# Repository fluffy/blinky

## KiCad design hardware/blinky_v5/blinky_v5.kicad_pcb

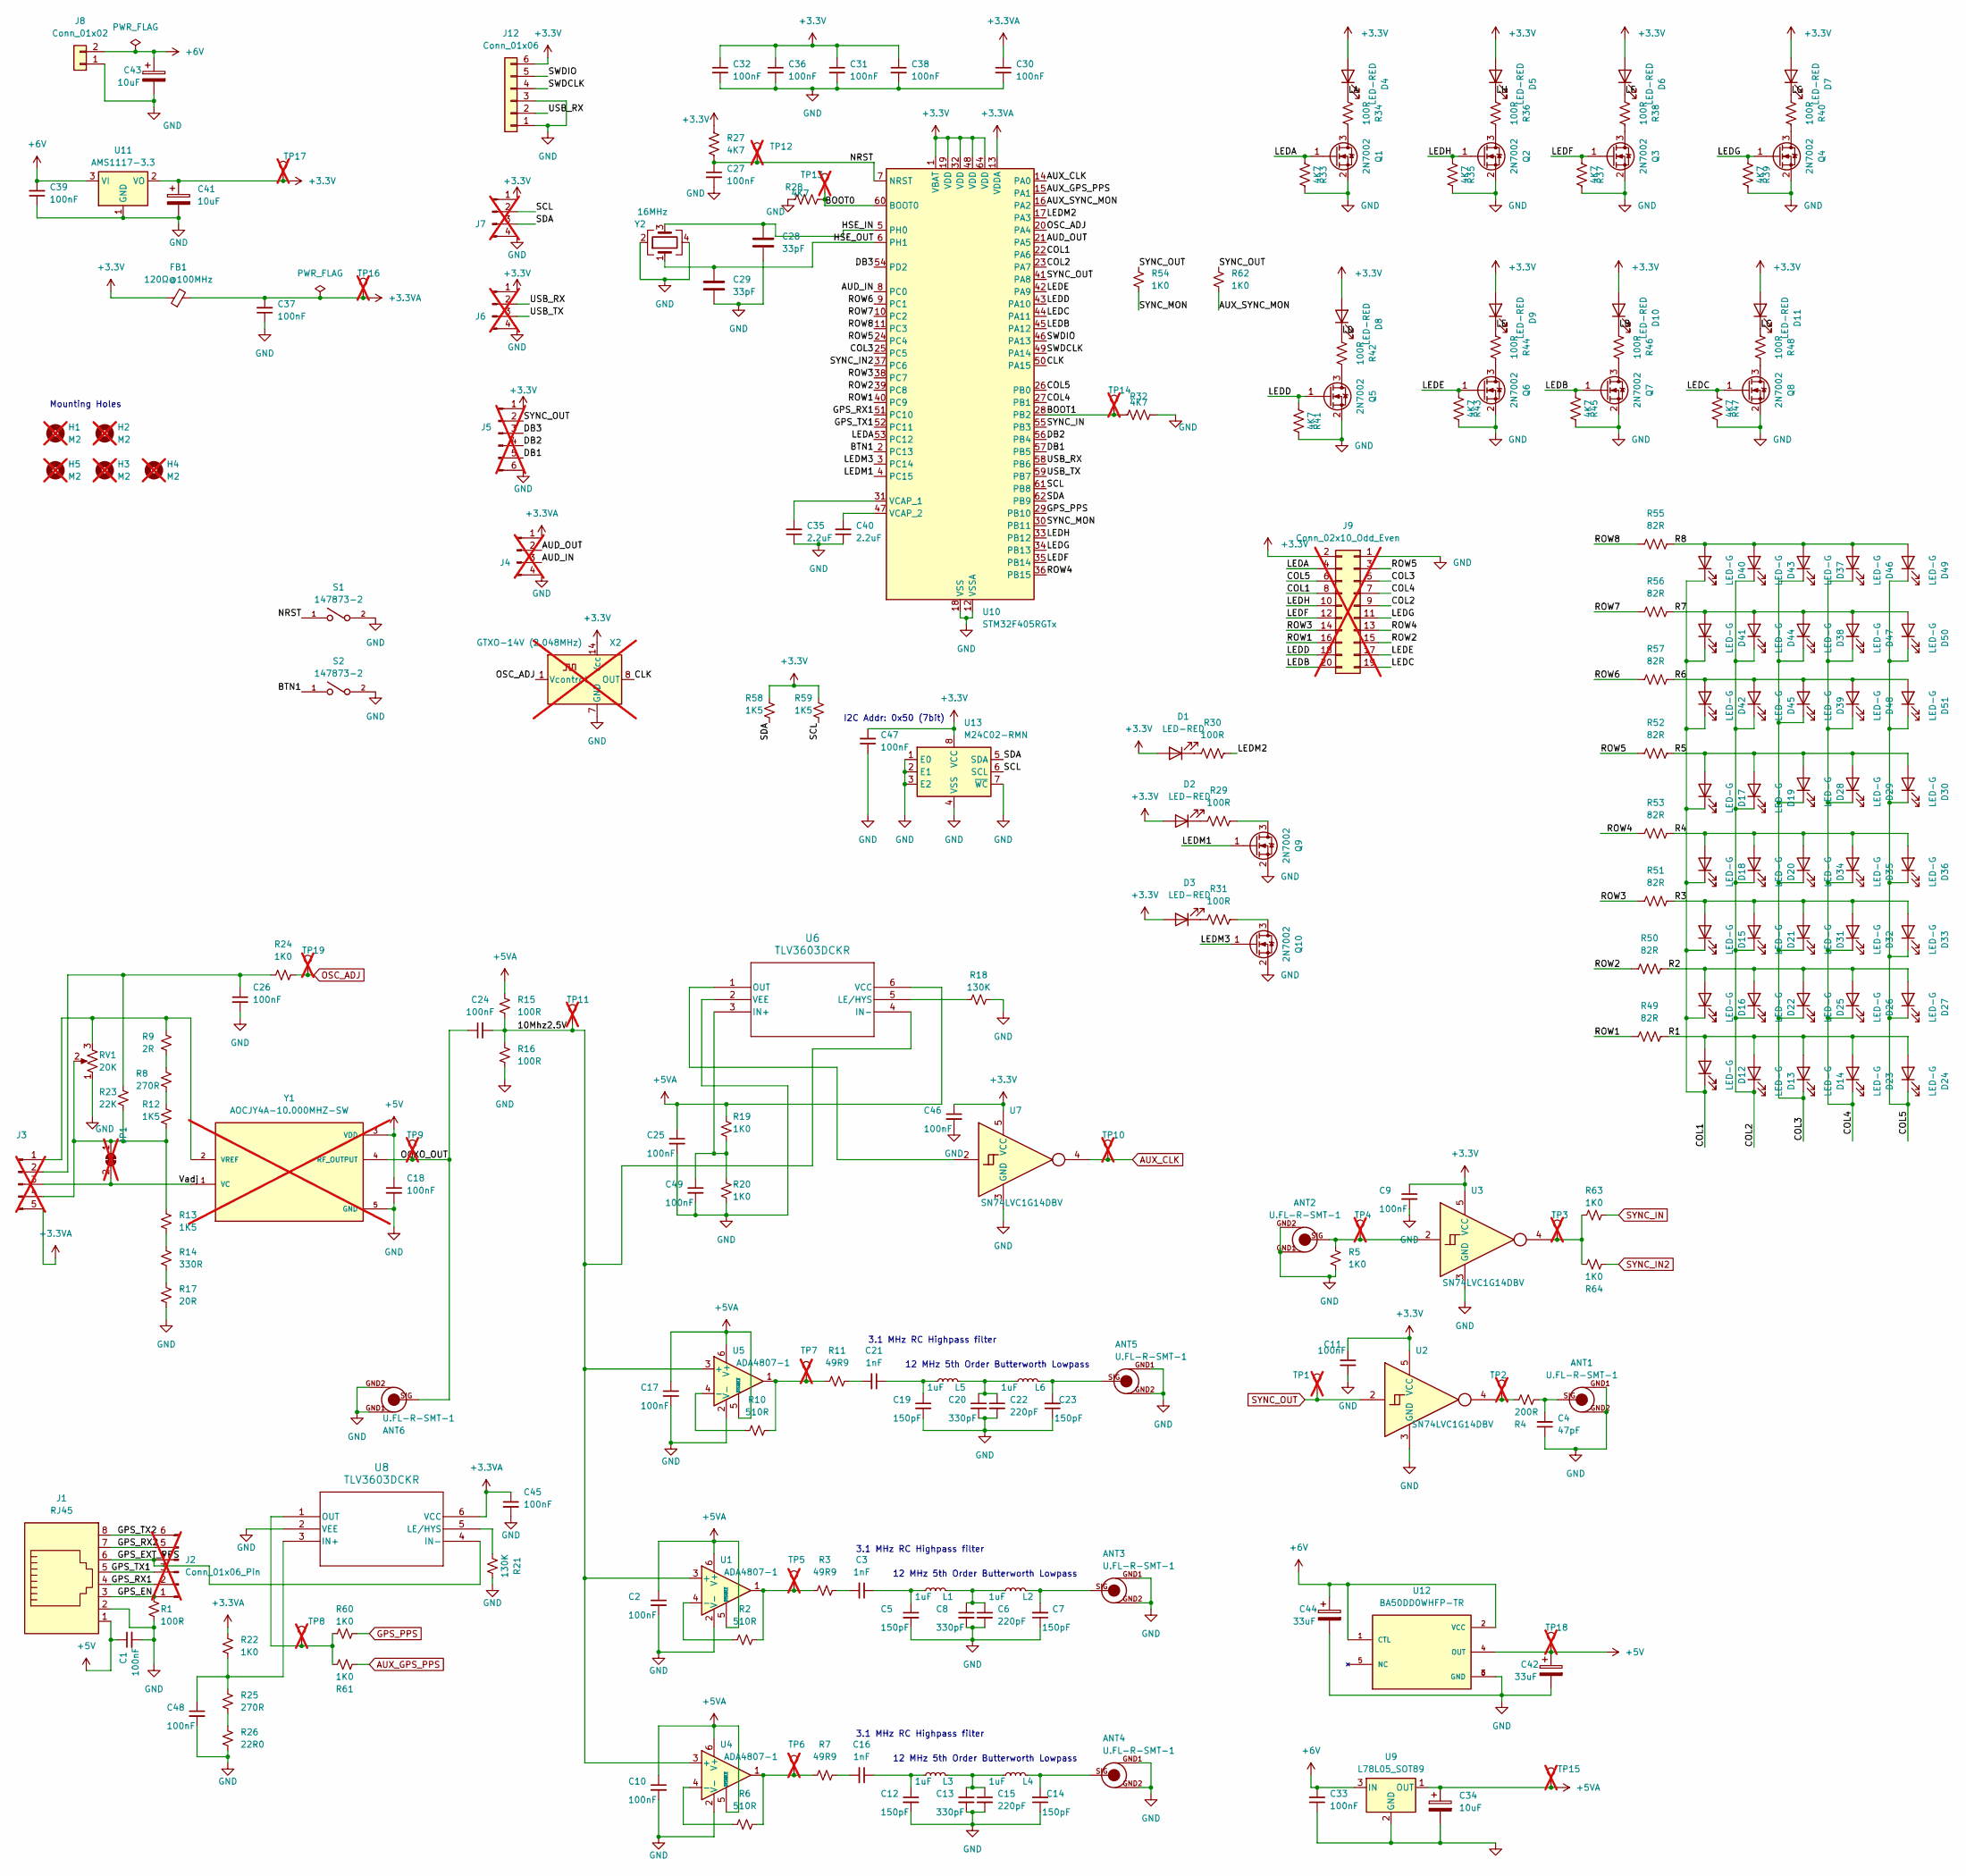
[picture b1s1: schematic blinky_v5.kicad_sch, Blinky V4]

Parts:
ANT1, ANT2, ANT3, ANT4, ANT5, ANT6: U.FL-R-SMT-1; LCSC C88374
C1, C2, C9, C10, C11, C17, C18, C25, C26, C30, C31, C32, C33, C36, C38, C39, C45, C46, C47, C48, C49: 100nF; C_0402_1005Metric; LCSC C307331
C3, C16, C21: 1nF; C_0603_1608Metric; LCSC C1588
C4: 47pF; C_0805_2012Metric; LCSC C14857
C5, C7, C12, C14, C19, C23: 150pF; C_0603_1608Metric; LCSC C1594
C6, C15, C22: 220pF; C_0603_1608Metric; LCSC C1603
C8, C13, C20: 330pF; C_0603_1608Metric; LCSC C1664
C24, C27, C37: 100nF; C_0603_1608Metric; LCSC C14663
C28, C29: 33pF; C_0603_1608Metric; LCSC C1663
C34, C41, C43: 10uF; CP_EIA-3216-18_Kemet-A; LCSC C7171
C35, C40: 2.2uF; C_0603_1608Metric; LCSC C23630
C42, C44: 33uF; CP_EIA-3528-21_Kemet-B; LCSC C128342
D1, D2, D3, D4, D5, D6, D7, D8, D9, D10, D11: LED-RED; LED_0603_1608Metric; LCSC C94869
D12, D13, D14, D15, D16, D17, D18, D19, D20, D21, D22, D23, D24, D25, D26, D27, D28, D29, D30, D31, D32, D33, D34, D35, D36, D37, D38, D39, D40, D41, D42, D43, D44, D45, D46, D47, D48, D49, D50, D51: LED-G; LED_0603_1608Metric; LCSC C125093
FB1: 120Ω@100MHz; R_0603_1608Metric; LCSC C127301
H1, H2, H3, H4, H5: M2; MountingHole_2.2mm_M2; not fitted
J1: RJ45; RJ45_Amphenol_RJHSE5380; LCSC C464586
J2, J5: Conn_01x06_Pin; PinHeader_1x06_P2.54mm_Vertical; not fitted
J3: Conn_01x05_Pin; PinHeader_1x05_P2.54mm_Vertical; not fitted
J4, J6, J7: Conn_01x04_Pin; PinHeader_1x04_P2.54mm_Vertical; not fitted
J8: Conn_01x02; JST_PH_S2B-PH-SM4-TB_1x02-1MP_P2.00mm_Horizontal; LCSC C295747
J9: Conn_02x10_Odd_Even; PinHeader_2x10_P2.54mm_Vertical; not fitted
J12: Conn_01x06; JST_PH_S6B-PH-SM4-TB_1x06-1MP_P2.00mm_Horizontal; LCSC C265405
JP1: SolderJumper_2_Bridged; SolderJumper-2_P1.3mm_Bridged_RoundedPad1.0x1.5mm; not fitted
L1, L2, L3, L4, L5, L6: 1uF; L_0805_2012Metric; LCSC C1042
Q1, Q2, Q3, Q4, Q5, Q6, Q7, Q8, Q9, Q10: 2N7002; SOT-23; LCSC C8545
R1, R15, R16, R29, R30, R31, R34, R36, R38, R40, R42, R44, R46, R48: 100R; R_0603_1608Metric; LCSC C22775
R2, R6, R10: 510R; R_0603_1608Metric; LCSC C23193
R3, R7, R11: 49R9; R_0603_1608Metric; LCSC C23185
R4: 200R; R_0805_2012Metric; LCSC C17540
R5, R19, R20, R22, R24, R54, R60, R61, R62, R63, R64: 1K0; R_0603_1608Metric; LCSC C21190
R8: 270R; R_0805_2012Metric; LCSC C17590
R9: 2R; R_0805_2012Metric; LCSC C17606
R12, R13: 1K5; R_0805_2012Metric; LCSC C4310
R14: 330R; R_0805_2012Metric; LCSC C17630
R17: 20R; R_0805_2012Metric; LCSC C17544
R18, R21: 130K; R_0603_1608Metric; LCSC C22795
R23: 22K; R_0805_2012Metric; LCSC C17560
R25: 270R; R_0603_1608Metric; LCSC C22966
R26: 22R0; R_0603_1608Metric; LCSC C23345
R27, R28, R32, R33, R35, R37, R39, R41, R43, R45, R47: 4K7; R_0603_1608Metric; LCSC C23162
R49, R50, R51, R52, R53, R55, R56, R57: 82R; R_0603_1608Metric; LCSC C23255
R58, R59: 1K5; R_0603_1608Metric; LCSC C22843
RV1: 20K; Potentiometer_Bourns_3314G_Vertical; LCSC C780217
S1, S2: 147873-2; SW_147873-2
TP1, TP2, TP3, TP4, TP5, TP6, TP7, TP8, TP9, TP10, TP11, TP12, TP13, TP14, TP15, TP16, TP17, TP18, TP19: TestPoint_THTPad_D1.5mm_Drill0.7mm; not fitted
U1, U4, U5: ADA4807-1; SOT-23-6; LCSC C2058411
U2, U3, U7: SN74LVC1G14DBV; SOT-23-5; LCSC C133145
U6, U8: TLV3603DCKR; SC70_DCK_TEX; LCSC C5213955
U9: L78L05_SOT89; SOT-89-3; LCSC C71136
U10: STM32F405RGTx; LQFP-64_10x10mm_P0.5mm; LCSC C15742
U11: AMS1117-3.3; SOT-223-3_TabPin2; LCSC C6186
U12: BA50DD0WHFP-TR; DPAK172P1054X200-6N; PARTREV 003; LCSC C509718
U13: M24C02-RMN; SOIC-8_3.9x4.9mm_P1.27mm; LCSC C83836
X2: GTXO-14V (2.048MHz); Oscillator_DIP-14; not fitted
Y1: AOCJY4A-10.000MHZ-SW; XTAL_AOCJY4A-10.000MHZ-SW; PARTREV 07.24.11; LCSC C1670487; not fitted
Y2: 16MHz; Crystal_SMD_3225-4Pin_3.2x2.5mm; LCSC C13738

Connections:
+3.3V: C9.1, C11.1, C31.1, C32.1, C36.1, C38.1, C41.1, C46.1, C47.2, D1.2 (A), D2.2 (A), D3.2 (A), D4.2 (A), D5.2 (A), D6.2 (A), D7.2 (A), D8.2 (A), D9.2 (A), D10.2 (A), D11.2 (A), FB1.1, J5.1, J6.1, J7.1, J9.2, J12.6, R27.1, R58.1, R59.1, TP17.1, U2.5 (VCC), U3.5 (VCC), U7.5 (VCC), U10.1 (VBAT), U10.19 (VDD), U10.32 (VDD), U10.48 (VDD), U10.64 (VDD), U11.2 (VO), U13.8 (VCC), X2.14 (Vcc)
+3.3VA: C30.1, C37.2, C45.1, FB1.2, J3.5, J4.1, R22.1, TP16.1, U8.6 (VCC), U10.13 (VDDA)
+5V: C1.1, C18.1, C42.1, J1.1, TP18.1, U12.4 (OUT), Y1.3 (VDD)
+5VA: C2.1, C10.1, C17.1, C25.1, C34.1, R15.1, R19.1, TP15.1, U1.5 (~DISABLE), U1.6 (V+), U4.5 (~DISABLE), U4.6 (V+), U5.5 (~DISABLE), U5.6 (V+), U6.6 (VCC), U9.1 (OUT)
+6V: C33.2, C39.2, C43.1, C44.1, J8.2, U9.3 (IN), U11.3 (VI), U12.1 (CTL), U12.2 (VCC)
/10Mhz2.5V: C24.2, R15.2, R16.1, TP11.1, U1.3 (+), U4.3 (+), U5.3 (+), U6.4 (IN-)
/AUD_IN: J4.3, U10.8 (PC0)
/AUD_OUT: J4.2, U10.21 (PA5)
/AUX_SYNC_MON: R62.2, U10.16 (PA2)
/BOOT0: R28.1, TP13.1, U10.60 (BOOT0)
/BOOT1: R32.2, TP14.1, U10.28 (PB2)
/BTN1: S2.1, U10.2 (PC13)
/CLK: U10.50 (PA15), X2.8 (OUT)
/COL1: D12.1 (K), D15.1 (K), D16.1 (K), D17.1 (K), D18.1 (K), D40.1 (K), D41.1 (K), D42.1 (K), J9.8, U10.22 (PA6)
/COL2: D13.1 (K), D19.1 (K), D20.1 (K), D21.1 (K), D22.1 (K), D43.1 (K), D44.1 (K), D45.1 (K), J9.9, U10.23 (PA7)
/COL3: D14.1 (K), D25.1 (K), D28.1 (K), D31.1 (K), D34.1 (K), D37.1 (K), D38.1 (K), D39.1 (K), J9.5, U10.25 (PC5)
/COL4: D23.1 (K), D26.1 (K), D29.1 (K), D32.1 (K), D35.1 (K), D46.1 (K), D47.1 (K), D48.1 (K), J9.7, U10.27 (PB1)
/COL5: D24.1 (K), D27.1 (K), D30.1 (K), D33.1 (K), D36.1 (K), D49.1 (K), D50.1 (K), D51.1 (K), J9.6, U10.26 (PB0)
/DB1: J5.5, U10.57 (PB5)
/DB2: J5.4, U10.56 (PB4)
/DB3: J5.3, U10.54 (PD2)
/GPS_EN: J1.3, J2.1, R1.1
/GPS_EXT_PPS: J1.6, J2.4, U8.4 (IN-)
/GPS_RX1: J1.4, J2.2, U10.51 (PC10)
/GPS_RX2: J1.7, J2.5
/GPS_TX1: J1.5, J2.3, U10.52 (PC11)
/GPS_TX2: J1.8, J2.6
/HSE_IN: C28.1, U10.5 (PH0), Y2.3
/HSE_OUT: C29.1, U10.6 (PH1), Y2.1
/LA: D4.1 (K), R34.1
/LB: D10.1 (K), R46.1
/LC: D11.1 (K), R48.1
/LD: D8.1 (K), R42.1
/LE: D9.1 (K), R44.1
/LEDA: J9.4, Q1.1 (G), R33.2, U10.53 (PC12)
/LEDB: J9.20, Q7.1 (G), R45.2, U10.45 (PA12)
/LEDC: J9.19, Q8.1 (G), R47.2, U10.44 (PA11)
/LEDD: J9.18, Q5.1 (G), R41.2, U10.43 (PA10)
/LEDE: J9.17, Q6.1 (G), R43.2, U10.42 (PA9)
/LEDF: J9.12, Q3.1 (G), R37.2, U10.35 (PB14)
/LEDG: J9.11, Q4.1 (G), R39.2, U10.34 (PB13)
/LEDH: J9.10, Q2.1 (G), R35.2, U10.33 (PB12)
/LEDM1: Q9.1 (G), U10.4 (PC15)
/LEDM2: R30.2, U10.17 (PA3)
/LEDM3: Q10.1 (G), U10.3 (PC14)
/LF: D6.1 (K), R38.1
/LG: D7.1 (K), R40.1
/LH: D5.1 (K), R36.1
/NRST: C27.1, R27.2, S1.1, TP12.1, U10.7 (NRST)
/OCXO_OUT: ANT6.SIG, C24.1, TP9.1, Y1.4 (RF_OUTPUT)
/R1: D12.2 (A), D13.2 (A), D14.2 (A), D23.2 (A), D24.2 (A), R49.1
/R2: D16.2 (A), D22.2 (A), D25.2 (A), D26.2 (A), D27.2 (A), R50.1
/R3: D15.2 (A), D21.2 (A), D31.2 (A), D32.2 (A), D33.2 (A), R51.1
/R4: D18.2 (A), D20.2 (A), D34.2 (A), D35.2 (A), D36.2 (A), R53.1
/R5: D17.2 (A), D19.2 (A), D28.2 (A), D29.2 (A), D30.2 (A), R52.1
/R6: D39.2 (A), D42.2 (A), D45.2 (A), D48.2 (A), D51.2 (A), R57.1
/R7: D38.2 (A), D41.2 (A), D44.2 (A), D47.2 (A), D50.2 (A), R56.1
/R8: D37.2 (A), D40.2 (A), D43.2 (A), D46.2 (A), D49.2 (A), R55.1
/ROW1: J9.16, R49.2, U10.40 (PC9)
/ROW2: J9.15, R50.2, U10.39 (PC8)
/ROW3: J9.14, R51.2, U10.38 (PC7)
/ROW4: J9.13, R53.2, U10.36 (PB15)
/ROW5: J9.3, R52.2, U10.24 (PC4)
/ROW6: R57.2, U10.9 (PC1)
/ROW7: R56.2, U10.10 (PC2)
/ROW8: R55.2, U10.11 (PC3)
/SCL: J7.2, R59.2, U10.61 (PB8), U13.6 (SCL)
/SDA: J7.3, R58.2, U10.62 (PB9), U13.5 (SDA)
/SWDCLK: J12.4, U10.49 (PA14)
/SWDIO: J12.5, U10.46 (PA13)
/SYNC_MON: R54.2, U10.30 (PB11)
/USB_RX: J6.2, J12.2, U10.58 (PB6)
/USB_TX: J6.3, U10.59 (PB7)
/Vadj: J3.3, JP1.2 (B), Y1.1 (VC)
AUX_CLK: TP10.1, U7.4, U10.14 (PA0)
AUX_GPS_PPS: R61.2, U10.15 (PA1)
GND: ANT1.GND1, ANT1.GND2, ANT2.GND1, ANT2.GND2, ANT3.GND1, ANT3.GND2, ANT4.GND1, ANT4.GND2, ANT5.GND1, ANT5.GND2, ANT6.GND1, ANT6.GND2, C1.2, C2.2, C4.1, C5.2, C6.2, C7.1, C8.2, C9.2, C10.2, C11.2, C12.2, C13.2, C14.1, C15.2, C17.2, C18.2, C19.2, C20.2, C22.2, C23.1, C25.2, C26.2, C27.2, C28.2, C29.2, C30.2, C31.2, C32.2, C33.1, C34.2, C35.1, C36.2, C37.1, C38.2, C39.1, C40.1, C41.2, C42.2, C43.2, C44.2, C45.2, C46.2, C47.1, C48.2, C49.2, J1.2, J4.4, J5.6, J6.4, J7.4, J8.1, J9.1, J12.1, J12.3, Q1.2 (S), Q2.2 (S), Q3.2 (S), Q4.2 (S), Q5.2 (S), Q6.2 (S), Q7.2 (S), Q8.2 (S), Q9.2 (S), Q10.2 (S), R1.2, R5.2, R16.2, R17.2, R18.2, R20.2, R21.2, R26.2, R28.2, R32.1, R33.1, R35.1, R37.1, R39.1, R41.1, R43.1, R45.1, R47.1, RV1.1, S1.2, S2.2, U1.2 (V-), U2.3 (GND), U3.3 (GND), U4.2 (V-), U5.2 (V-), U6.2 (VEE), U7.3 (GND), U8.2 (VEE), U9.2 (GND), U10.12 (VSSA), U10.18 (VSS), U10.63 (VSS), U11.1 (GND), U12.3 (GND), U12.6 (GND), U13.1 (E0), U13.2 (E1), U13.3 (E2), U13.4 (VSS), U13.7 (~WC), X2.7 (GND), Y1.5 (GND), Y2.2, Y2.4
GPS_PPS: R60.1, U10.29 (PB10)
unnamed: ANT1.SIG, C4.2, R4.2
unnamed: ANT2.SIG, R5.1, TP4.1, U3.2
unnamed: ANT3.SIG, C7.2, L2.1
unnamed: ANT4.SIG, C14.2, L4.1
unnamed: ANT5.SIG, C23.2, L6.1
unnamed: C3.1, C5.1, L1.1
unnamed: C3.2, R3.2
unnamed: C6.1, C8.1, L1.2, L2.2
unnamed: C12.1, C16.1, L3.1
unnamed: C13.1, C15.1, L3.2, L4.2
unnamed: C16.2, R7.2
unnamed: C19.1, C21.1, L5.1
unnamed: C20.1, C22.1, L5.2, L6.2
unnamed: C21.2, R11.2
unnamed: D1.1 (K), R30.1
unnamed: D2.1 (K), R29.1
unnamed: D3.1 (K), R31.1
unnamed: J3.1, R9.1, RV1.3, Y1.2 (VREF)
unnamed: C26.1, J3.2, R23.1, R24.1
unnamed: J3.4, JP1.1 (A), R12.2, R13.1, R23.2, RV1.2
unnamed: Q1.3 (D), R34.2
unnamed: Q2.3 (D), R36.2
unnamed: Q3.3 (D), R38.2
unnamed: Q4.3 (D), R40.2
unnamed: Q5.3 (D), R42.2
unnamed: Q6.3 (D), R44.2
unnamed: Q7.3 (D), R46.2
unnamed: Q8.3 (D), R48.2
unnamed: Q9.3 (D), R29.2
unnamed: Q10.3 (D), R31.2
unnamed: R2.2, R3.1, TP5.1, U1.1
unnamed: R4.1, TP2.1, U2.4
unnamed: R6.2, R7.1, TP6.1, U4.1
unnamed: R8.1, R9.2
unnamed: R10.2, R11.1, TP7.1, U5.1
unnamed: R8.2, R12.1
unnamed: R13.2, R14.1
unnamed: R14.2, R17.1
unnamed: R25.2, R26.1
unnamed: R63.2, R64.2, TP3.1, U3.4
unnamed: R2.1, U1.4 (-)
unnamed: R6.1, U4.4 (-)
unnamed: R10.1, U5.4 (-)
unnamed: C49.1, R19.2, R20.1, U6.3 (IN+)
unnamed: R18.1, U6.5 (LE/HYS)
unnamed: U6.1 (OUT), U7.2
unnamed: C48.1, R22.2, R25.1, U8.3 (IN+)
unnamed: R21.1, U8.5 (LE/HYS)
unnamed: R60.2, R61.1, TP8.1, U8.1 (OUT)
unnamed: C35.2, U10.31 (VCAP_1)
unnamed: C40.2, U10.47 (VCAP_2)
OSC_ADJ: R24.2, TP19.1, U10.20 (PA4), X2.1 (Vcontrol)
SYNC_IN: R63.1, U10.55 (PB3)
SYNC_IN2: R64.1, U10.37 (PC6)
SYNC_OUT: J5.2, R54.1, R62.1, TP1.1, U2.2, U10.41 (PA8)

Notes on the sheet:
3.1 MHz RC Highpass filter
12 MHz 5th Order Butterworth Lowpass
I2C Addr: 0x50 (7bit)
Mounting Holes

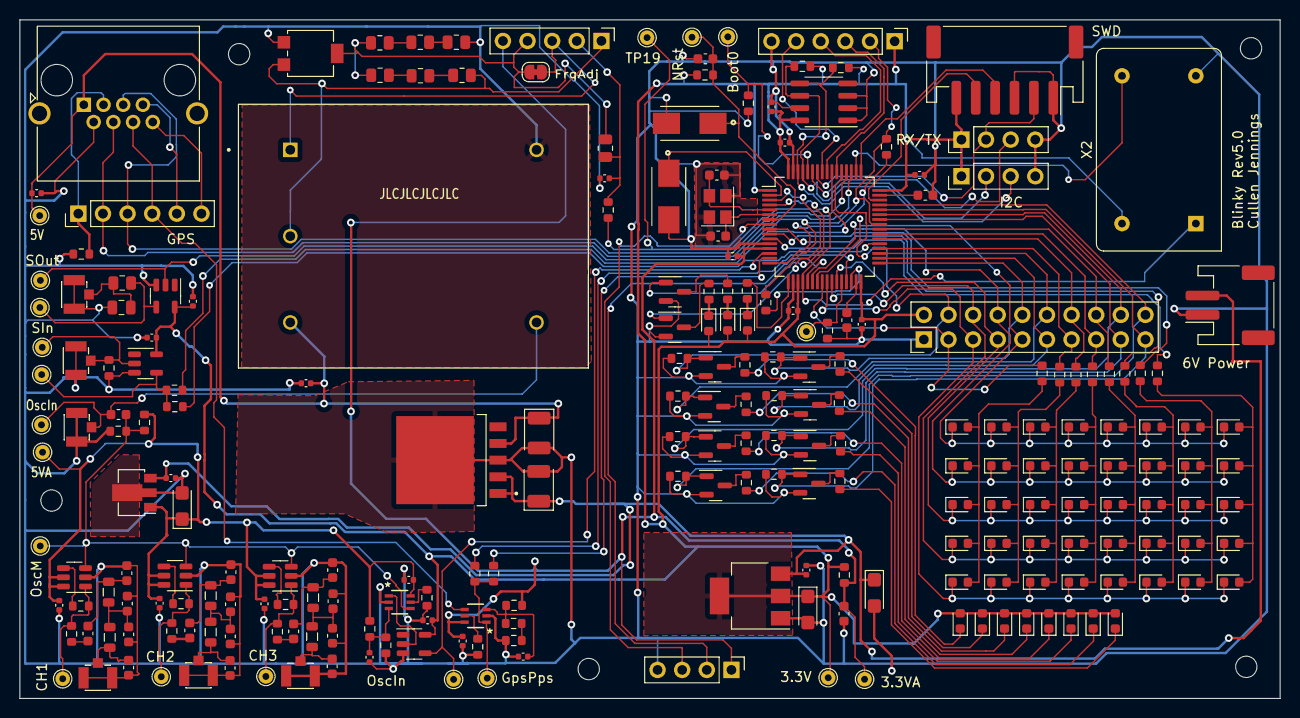
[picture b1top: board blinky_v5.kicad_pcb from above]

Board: 2 copper layers, 130.0 x 70.0 mm, 241 parts (0 on the bottom side), 133 nets.

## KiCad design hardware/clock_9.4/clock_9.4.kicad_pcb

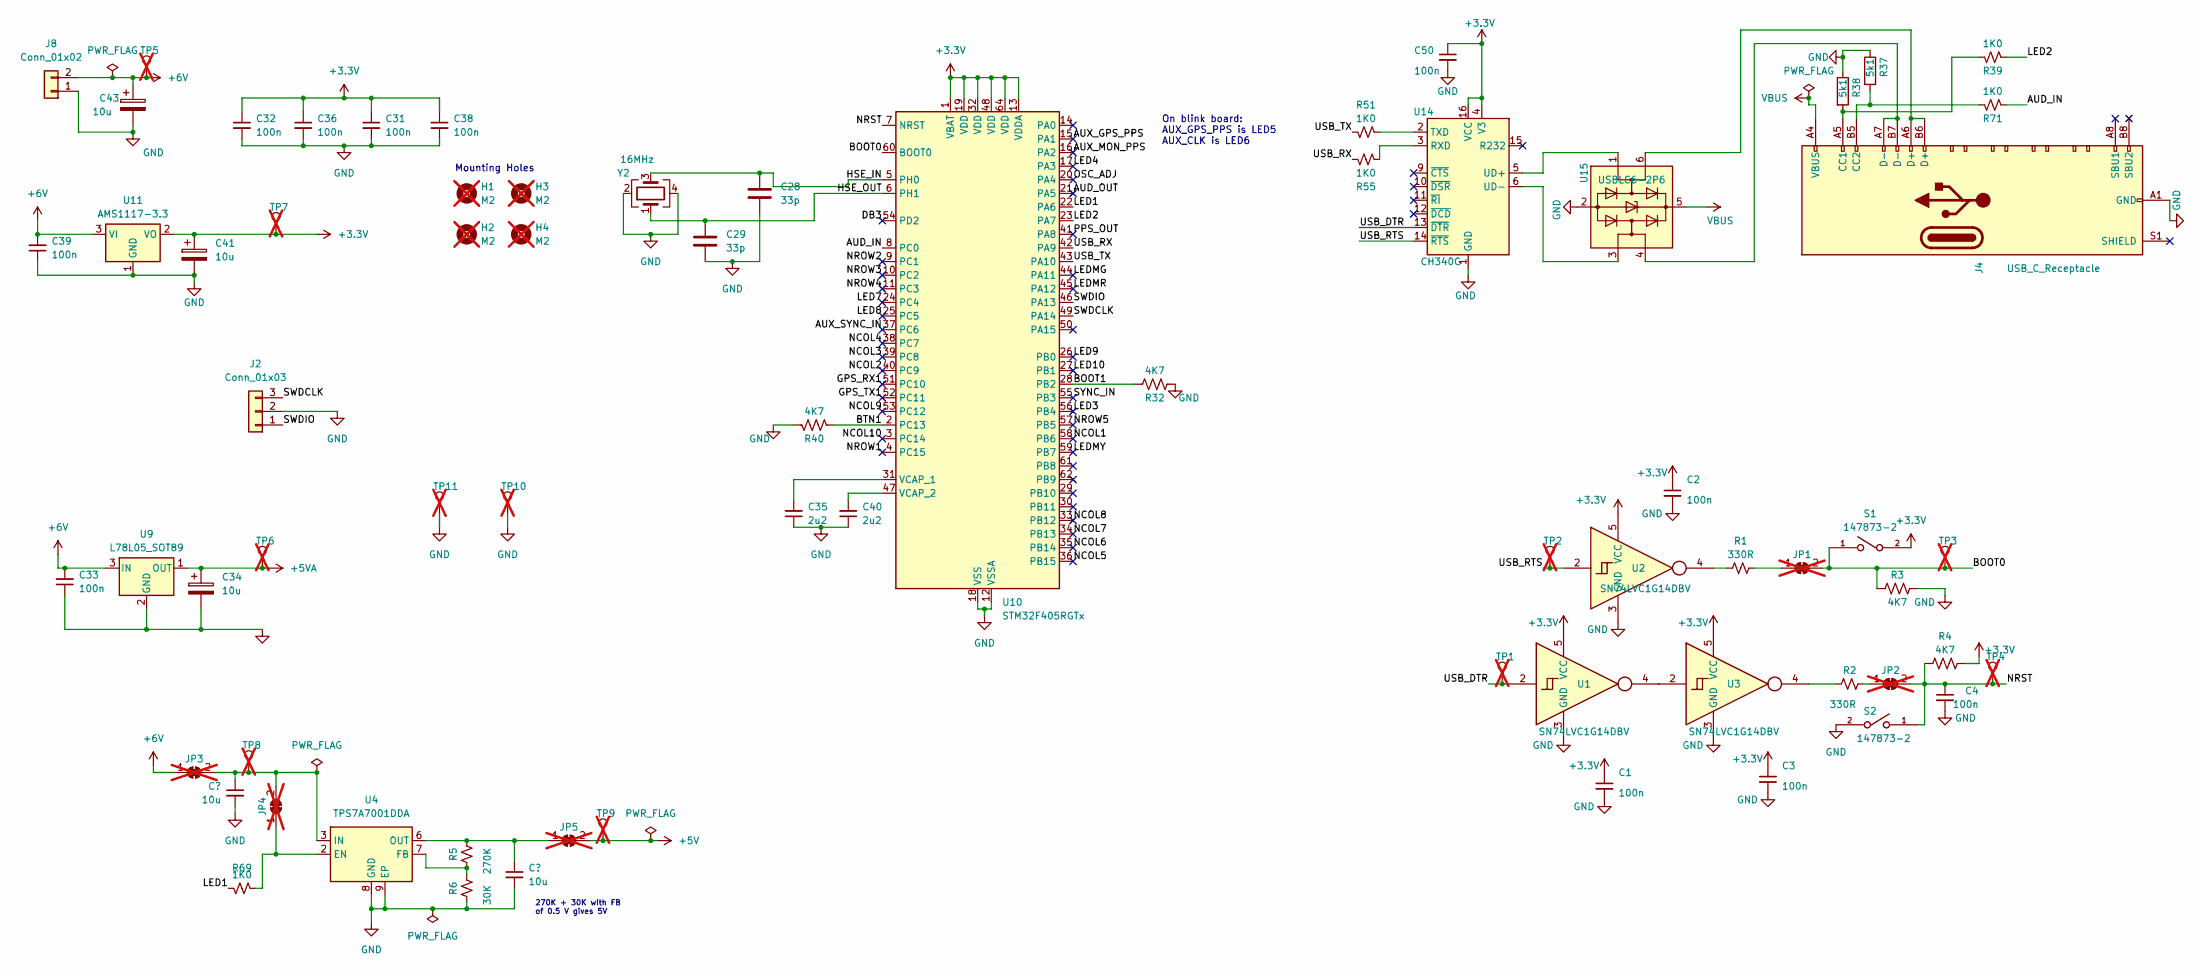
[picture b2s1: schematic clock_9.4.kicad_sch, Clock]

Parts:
C1, C2, C3, C31, C32, C33, C36, C38, C39, C50: 100n; C_0402_1005Metric; JLCPCB Part # C307331
C4: 100n; C_0603_1608Metric; JLCPCB Part # C14663
C5, C6: 10u; C_0603_1608Metric; JLCPCB Part # C19702
C28, C29: 33p; C_0603_1608Metric; JLCPCB Part # C1663
C34, C41, C43: 10u; CP_EIA-3216-18_Kemet-A; JLCPCB Part # C7171
C35, C40: 2u2; C_0603_1608Metric; JLCPCB Part # C23630
H1, H2, H3, H4: M2; MountingHole_2.2mm_M2; not fitted
J2: Conn_01x03; JST_PH_S3B-PH-SM4-TB_1x03-1MP_P2.00mm_Horizontal; JLCPCB Part # C265101
J4: USB_C_Receptacle; USB_C_Receptacle_HRO_TYPE-C-31-M-12; JLCPCB Part # C165948
J8: Conn_01x02; JST_PH_S2B-PH-SM4-TB_1x02-1MP_P2.00mm_Horizontal; JLCPCB Part # C295747
JP1, JP2, JP3, JP4, JP5: SolderJumper_2_Bridged; SolderJumper-2_P1.3mm_Bridged2Bar_RoundedPad1.0x1.5mm; not fitted
R1, R2: 330R; R_0603_1608Metric; JLCPCB Part # C23138
R3, R4, R32, R40: 4K7; R_0603_1608Metric; JLCPCB Part # C23162
R5: 270K; R_0603_1608Metric; JLCPCB Part # C22966
R6: 30K; R_0603_1608Metric; JLCPCB Part # C22984
R37, R38: 5k1; R_0603_1608Metric; JLCPCB Part # C23186
R39, R51, R55, R69, R71: 1K0; R_0603_1608Metric; JLCPCB Part # C21190
S1, S2: 147873-2; SW_147873-2; JLCPCB Part # C266189
TP1, TP2, TP3, TP4, TP5, TP6, TP7, TP8, TP9, TP10, TP11: TestPoint_THTPad_D1.5mm_Drill0.7mm; not fitted
U1, U2, U3: SN74LVC1G14DBV; SOT-23-5; JLCPCB Rotation Offset 0
U4: TPS7A7001DDA; TI_SO-PowerPAD-8; JLCPCB Part # C60719
U9: L78L05_SOT89; SOT-89-3; JLCPCB Rotation Offset 180
U10: STM32F405RGTx; LQFP-64_10x10mm_P0.5mm; JLCPCB Rotation Offset 270
U11: AMS1117-3.3; SOT-223-3_TabPin2; JLCPCB Rotation Offset 180
U14: CH340C; SOIC-16_3.9x9.9mm_P1.27mm; JLCPCB Part # C84681
U15: USBLC6-2P6; SOT-666; JLCPCB Part # C2827693
Y2: 16MHz; Crystal_SMD_3225-4Pin_3.2x2.5mm; JLCPCB Part # C13738

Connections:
+3.3V: C1.1, C2.1, C3.1, C31.1, C32.1, C36.1, C38.1, C41.1, C50.1, R4.1, S1.2, TP7.1, U1.5 (VCC), U2.5 (VCC), U3.5 (VCC), U10.1 (VBAT), U10.13 (VDDA), U10.19 (VDD), U10.32 (VDD), U10.48 (VDD), U10.64 (VDD), U11.2 (VO), U14.4 (V3), U14.16 (VCC)
+5V: JP5.2 (B), TP9.1
+5VA: C34.1, TP6.1, U9.1 (OUT)
+6V: C33.2, C39.2, C43.1, J8.2, JP3.1 (A), TP5.1, U9.3 (IN), U11.3 (VI)
/AUD_IN: R71.2, U10.8 (PC0)
/AUD_OUT: U10.21 (PA5)
/AUX_GPS_PPS: U10.15 (PA1)
/AUX_MON_PPS: U10.16 (PA2)
/AUX_SYNC_IN: U10.37 (PC6)
/BOOT0: JP1.2 (B), R3.1, S1.1, TP3.1, U10.60 (BOOT0)
/BOOT1: R32.2, U10.28 (PB2)
/BTN1: R40.2, U10.2 (PC13)
/DB3: U10.54 (PD2)
/GPS_RX1: U10.51 (PC10)
/GPS_TX1: U10.52 (PC11)
/HSE_IN: C28.1, U10.5 (PH0), Y2.3
/HSE_OUT: C29.1, U10.6 (PH1), Y2.1
/LED1: R69.2, U10.22 (PA6)
/LED2: R39.2, U10.23 (PA7)
/LED3: U10.56 (PB4)
/LED4: U10.17 (PA3)
/LED7: U10.24 (PC4)
/LED8: U10.25 (PC5)
/LED9: U10.26 (PB0)
/LED10: U10.27 (PB1)
/LEDMG: U10.44 (PA11)
/LEDMR: U10.45 (PA12)
/LEDMY: U10.59 (PB7)
/NCOL1: U10.58 (PB6)
/NCOL2: U10.40 (PC9)
/NCOL3: U10.39 (PC8)
/NCOL4: U10.38 (PC7)
/NCOL5: U10.36 (PB15)
/NCOL6: U10.35 (PB14)
/NCOL7: U10.34 (PB13)
/NCOL8: U10.33 (PB12)
/NCOL9: U10.53 (PC12)
/NCOL10: U10.3 (PC14)
/NROW1: U10.4 (PC15)
/NROW2: U10.9 (PC1)
/NROW3: U10.10 (PC2)
/NROW4: U10.11 (PC3)
/NROW5: U10.57 (PB5)
/NRST: C4.1, JP2.2 (B), R4.2, S2.1, TP4.1, U10.7 (NRST)
/OSC_ADJ: U10.20 (PA4)
/PPS_OUT: U10.41 (PA8)
/SWDCLK: J2.3, U10.49 (PA14)
/SWDIO: J2.1, U10.46 (PA13)
/SYNC_IN: U10.55 (PB3)
/USB_DTR: TP1.1, U1.2, U14.13 (~DTR)
/USB_RTS: TP2.1, U2.2, U14.14 (~RTS)
/USB_RX: R55.1, U10.42 (PA9)
/USB_TX: R51.2, U10.43 (PA10)
GND: C1.2, C2.2, C3.2, C4.2, C5.2, C6.2, C28.2, C29.2, C31.2, C32.2, C33.1, C34.2, C35.1, C36.2, C38.2, C39.1, C40.1, C41.2, C43.2, C50.2, J2.2, J4.A1 (GND), J4.A12 (GND), J4.B1 (GND), J4.B12 (GND), J8.1, R3.2, R6.2, R32.1, R37.1, R38.1, R40.1, S2.2, TP10.1, TP11.1, U1.3 (GND), U2.3 (GND), U3.3 (GND), U4.8 (GND), U4.9 (EP), U9.2 (GND), U10.12 (VSSA), U10.18 (VSS), U10.63 (VSS), U11.1 (GND), U14.1 (GND), U15.2 (GND), Y2.2, Y2.4
unnamed: J4.A5 (CC1), R38.2, R39.1
unnamed: J4.B5 (CC2), R37.2, R71.1
unnamed: J4.A6 (D+), J4.B6 (D+), U15.6 (I/O1)
unnamed: J4.A7 (D-), J4.B7 (D-), U15.4 (I/O2)
unnamed: JP1.1 (A), R1.2
unnamed: JP2.1 (A), R2.1
unnamed: C5.1, JP3.2 (B), JP4.2 (B), TP8.1, U4.3 (IN)
unnamed: JP4.1 (A), R69.1, U4.2 (EN)
unnamed: C6.1, JP5.1 (A), R5.1, U4.6 (OUT)
unnamed: R1.1, U2.4
unnamed: R2.2, U3.4
unnamed: U1.4, U3.2
unnamed: R5.2, R6.1, U4.7 (FB)
unnamed: C35.2, U10.31 (VCAP_1)
unnamed: C40.2, U10.47 (VCAP_2)
unnamed: R55.2, U14.3 (RXD)
unnamed: R51.1, U14.2 (TXD)
unnamed: U14.5 (UD+), U15.1 (I/O1)
unnamed: U14.6 (UD-), U15.3 (I/O2)
VBUS: J4.A4 (VBUS), J4.A9 (VBUS), J4.B4 (VBUS), J4.B9 (VBUS), U15.5 (VBUS)

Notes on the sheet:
On blink board: AUX_GPS_PPS is LED5 AUX_CLK is LED6
Mounting Holes
270K + 30K with FB of 0.5 V gives 5V

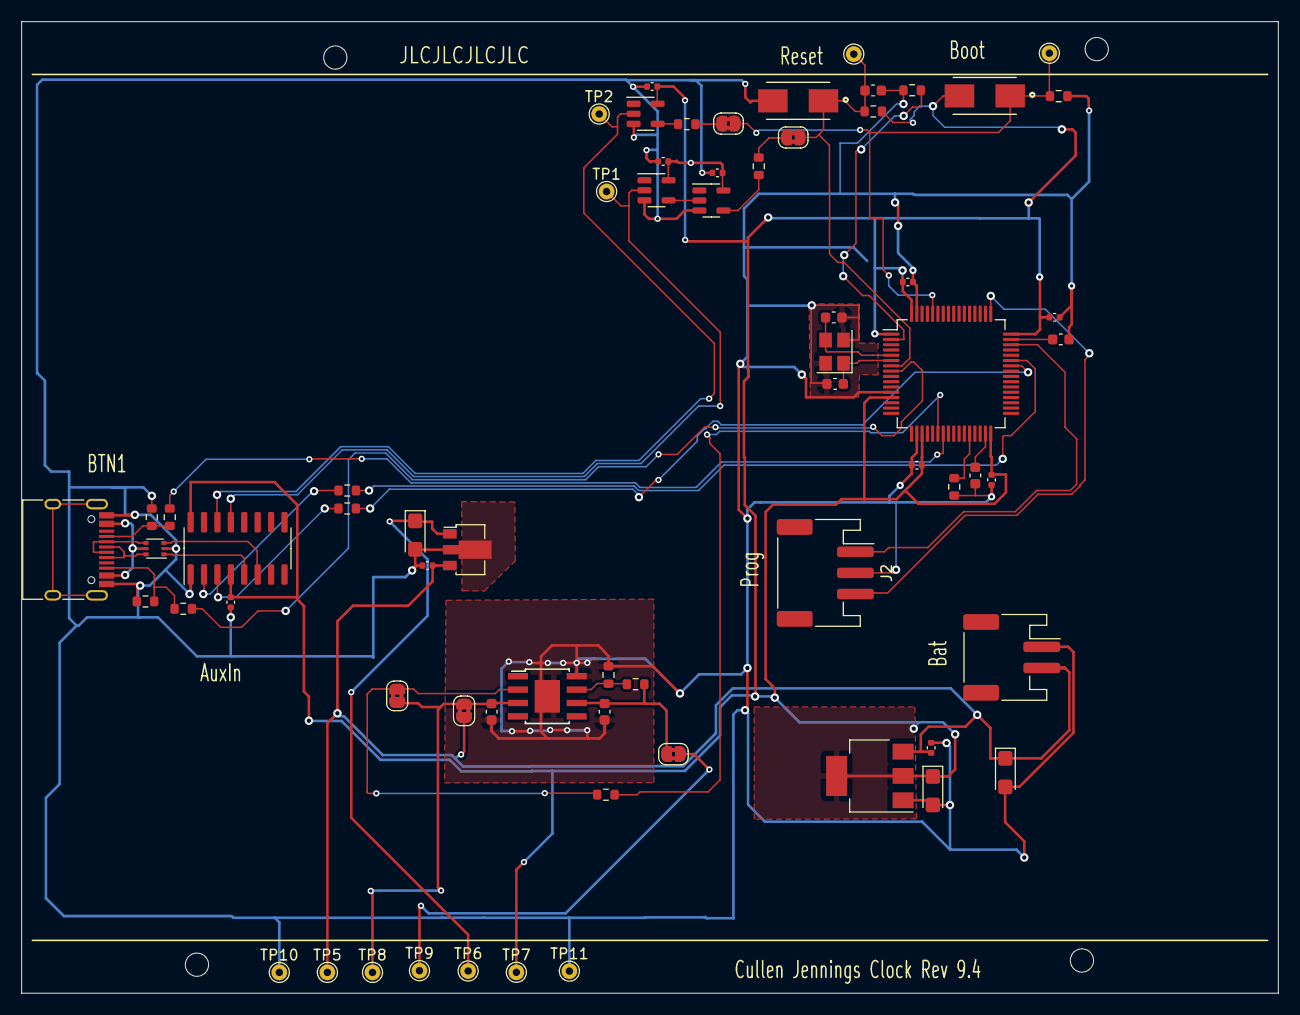
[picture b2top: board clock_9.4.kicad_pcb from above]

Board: 2 copper layers, 119.0 x 92.0 mm, 70 parts (0 on the bottom side), 40 nets.

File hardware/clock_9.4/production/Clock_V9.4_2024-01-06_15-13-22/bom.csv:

Designator,Footprint,Quantity,Value,LCSC Part #
"C1, C2, C3, C31, C32, C33, C36, C38, C39, C50",0402,10,100n,C307331
"C28, C29",0603,2,33p,C1663
"C34, C41, C43",CP_EIA-3216-18_Kemet-A,3,10u,C7171
"C35, C40",0603,2,2u2,C23630
C4,0603,1,100n,C14663
"C5, C6",0603,2,10u,C19702
J2,JST_PH_S3B-PH-SM4-TB_1x03-1MP_P2.00mm_Horizontal,1,Conn_01x03,C265101
J4,USB_C_Receptacle_HRO_TYPE-C-31-M-12,1,USB_C_Receptacle,C165948
J8,JST_PH_S2B-PH-SM4-TB_1x02-1MP_P2.00mm_Horizontal,1,Conn_01x02,C295747
"R1, R2",0603,2,330R,C23138
"R3, R32, R4, R40",0603,4,4K7,C23162
"R37, R38",0603,2,5k1,C23186
"R39, R51, R55, R69, R71",0603,5,1K0,C21190
R5,0603,1,270K,C22966
R6,0603,1,30K,C22984
"S1, S2",SW_147873-2,2,147873-2,C266189
"U1, U2, U3",SOT-23-5,3,SN74LVC1G14DBV,C133145
U10,LQFP-64_10x10mm_P0.5mm,1,STM32F405RGTx,C15742
U11,SOT-223-3_TabPin2,1,AMS1117-3.3,C6186
U14,SOIC-16_3.9x9.9mm_P1.27mm,1,CH340C,C84681
U15,SOT-666,1,USBLC6-2P6,C2827693
U4,TI_SO-PowerPAD-8,1,TPS7A7001DDA,C60719
U9,SOT-89-3,1,L78L05_SOT89,C71136
Y2,Crystal_SMD_3225-4Pin_3.2x2.5mm,1,16MHz ,C13738
